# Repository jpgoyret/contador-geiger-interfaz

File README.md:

# Interfaz de manejo y visualización de los datos de un contador Geiger-Müller en microcontrolador de 8 bits

## Descripcion:
Dispositivo para controlar y recibir información de un detector de partículas radioactivas. Este informa la cantidad de partículas que han sido recibidas en un intervalo de tiempo deseado y, en particular, comunica cuando se ha superado un umbral de radiación establecido por el usuario.

El primer prototipo funcional de este proyecto fue realizado en el marco de la materia "6609/8607 Laboratorio de Microcontroladores" en la Facultad de Ingeniería de la Universidad de Buenos Aires (FIUBA).

La intrerfaz fue desarrollada sobre un microcontrolador de 8 bits Atmega328p (integrado en un Arduino) y programada en Assembly.

## Navegación del repositorio

En el archivo [Documentacion_Contador_Geiger](Documentacion_Contador_Geiger.pdf) se podrá encontrar la documentación propia de la interfaz incluyendo: breve descripción del desarrollo, diagramas de flujo y de bloques, componentes de la interfaz, conexiones, entre otros.

En [Mediciones_Contador_Geiger](Mediciones_Contador_Geiger.pdf) se incluyen las mediciones realizadas sobre el contador Geiger por medio de la interfaz de manejo y visualización de datos. Para dichas pruebas se empleó una fuente elevadora de tensión elaborada por Ing. Ricardo Arias.

#### Carpetas:

- Codigo: incluye el código fuente del programa que irá embebido en el microcontrolador Atmega328p. Dicho código puede ser copiado y pegado dentro de la carpeta de un proyecto de Atmel Studio para poder ser modificado.
- diseño_caja_contador_geiger: contiene los archivos 3D del diseño de una caja que contenga a la fuente elevadora de tensión armada en una placa de 10cmx10cm.
- esquematicos: contiene los esquemáticos del PCB del shield del Arduino y del teclado.

## Integrantes del equipo:
- Nuñez Frau, Federico
- Vidal, Gabriel
- Goyret, Juan Pablo

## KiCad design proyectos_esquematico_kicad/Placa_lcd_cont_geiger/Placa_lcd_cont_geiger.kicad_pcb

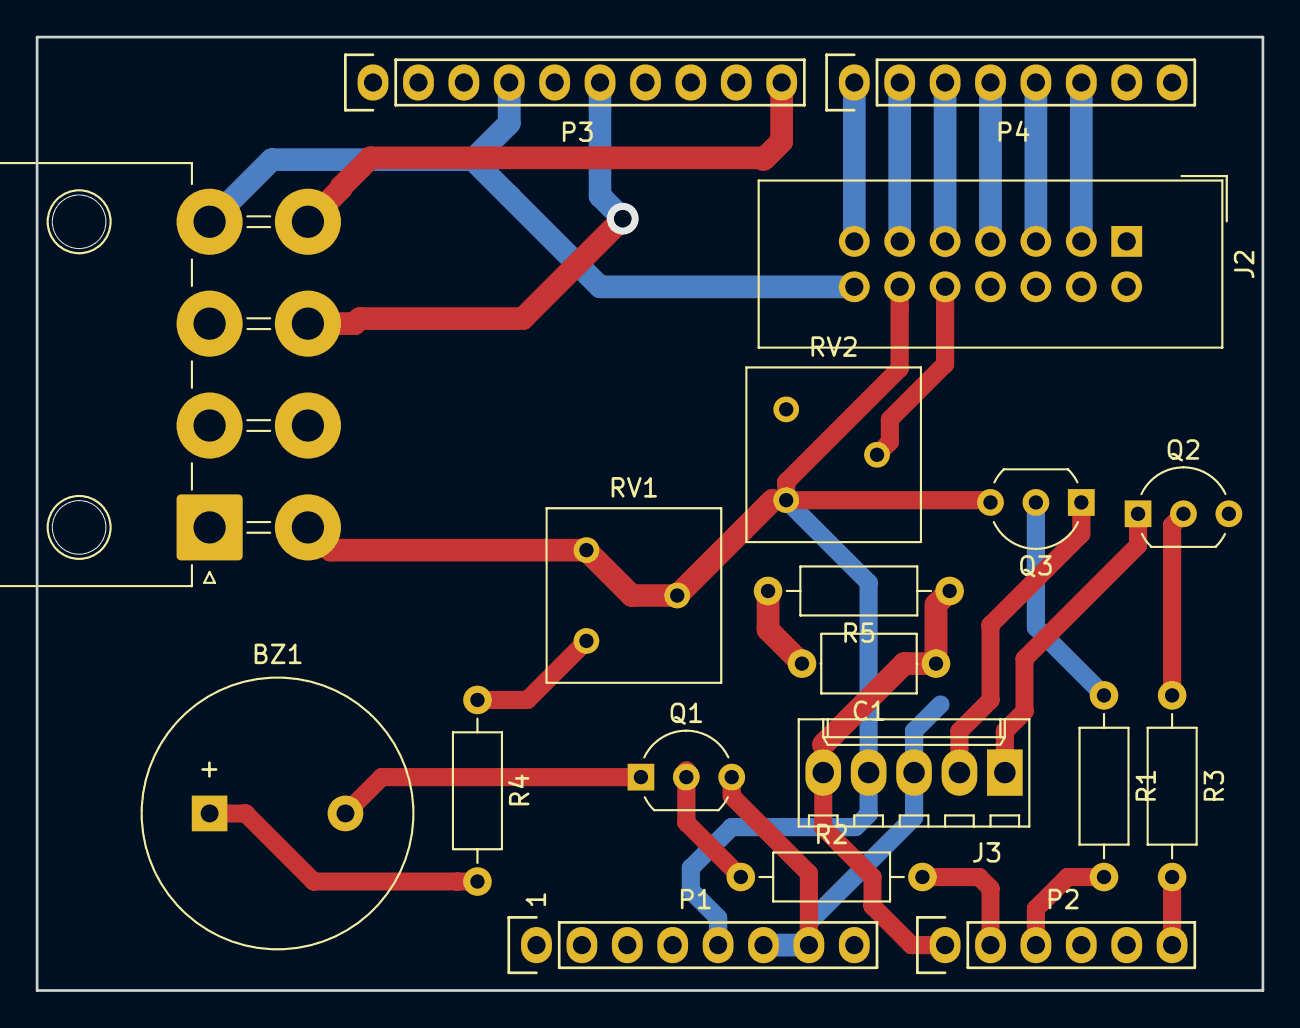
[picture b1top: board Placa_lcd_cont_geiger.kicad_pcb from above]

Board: 2 copper layers, 68.6 x 53.3 mm, 19 parts (0 on the bottom side), 23 nets.

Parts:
BZ1: Buzzer; Buzzer_15x7.5RM7.6
C1: 0.01u; C_Axial_L5.1mm_D3.1mm_P7.50mm_Horizontal
J1: Conn_02x04_Counter_Clockwise; Molex_Mega-Fit_76825-0008_2x04_P5.70mm_Horizontal
J2: Conn_01x14_Female; IDC-Header_2x07_P2.54mm_Vertical
J3: Conn_01x05_Female; Molex_KK-6410-05_05x2.54mm_Straight
P1: Power; Socket_Strip_Arduino_1x08
P2: Analog; Socket_Strip_Arduino_1x06
P3: Digital; Socket_Strip_Arduino_1x10
P4: Digital; Socket_Strip_Arduino_1x08
Q1, Q2: BC548; TO-92_Inline_Wide
Q3: BC558; TO-92_Inline_Wide
R1, R2, R3: 10k; R_Axial_DIN0207_L6.3mm_D2.5mm_P10.16mm_Horizontal
R4: 100; R_Axial_DIN0207_L6.3mm_D2.5mm_P10.16mm_Horizontal
R5: 100k; R_Axial_DIN0207_L6.3mm_D2.5mm_P10.16mm_Horizontal
RV1: 500; Potentiometer_Bourns_3386F_Vertical
RV2: 10k; Potentiometer_Bourns_3386F_Vertical

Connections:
/2: J2.3, P4.6
/3(**): J2.5, P4.5
/4: J2.7, P4.4
/5(**): J2.9, P4.3
/6(**): J2.11, P4.2
/7: J2.13, P4.1
/8: J1.8, P3.10
/12(MISO): J1.7, P3.6
/A0: C1.1, J3.5, P2.1, R5.1
/A1: P2.2, R2.2
/A2: P2.3, R1.2
/A5: P2.6, R3.2
GND: C1.2, J1.4, J2.14, J3.3, P1.6, P1.7, P3.4, Q1.3, Q2.3, R5.2, RV2.3
unnamed: BZ1.1, R4.2
unnamed: BZ1.2, Q1.1
unnamed: J2.10, RV2.2
unnamed: J3.1, Q2.1
unnamed: J3.2, Q3.1
unnamed: Q1.2, R2.1
unnamed: Q2.2, R3.1
unnamed: Q3.2, R1.1
unnamed: R4.1, RV1.1
VCC: J1.5, J2.12, J3.4, P1.5, Q3.3, RV1.2, RV1.3, RV2.1

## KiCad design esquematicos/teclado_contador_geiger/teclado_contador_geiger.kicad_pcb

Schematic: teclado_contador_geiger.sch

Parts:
D1: LED ROJO; LED_D5.0mm
D2: LED VERDE; LED_D5.0mm
J1: Conn_01x05_Female; Molex_KK-6410-05_05x2.54mm_Straight
R1: 82k; R_0805_2012Metric_Pad1.15x1.40mm_HandSolder
R2: 47k; R_0805_2012Metric_Pad1.15x1.40mm_HandSolder
R3: 33k; R_0805_2012Metric_Pad1.15x1.40mm_HandSolder
R4: 22k; R_0805_2012Metric_Pad1.15x1.40mm_HandSolder
R5: 15k; R_0805_2012Metric_Pad1.15x1.40mm_HandSolder
R6, R7: 220; R_0805_2012Metric_Pad1.15x1.40mm_HandSolder
SW1, SW2, SW3, SW4, SW5, SW6: SW_SPST; SW_PUSH_6mm

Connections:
+5V: J1.2, R6.1, SW1.2 (B), SW2.2 (B), SW3.2 (B), SW4.2 (B), SW5.2 (B), SW6.2 (B)
/teclado_out: J1.1, R5.2, SW6.1 (A)
GND: D2.1 (K), J1.3
unnamed: D1.1 (K), J1.5
unnamed: D1.2 (A), R6.2
unnamed: D2.2 (A), R7.2
unnamed: J1.4, R7.1
unnamed: R1.1, SW1.1 (A)
unnamed: R1.2, R2.1, SW2.1 (A)
unnamed: R2.2, R3.1, SW3.1 (A)
unnamed: R3.2, R4.1, SW4.1 (A)
unnamed: R4.2, R5.1, SW5.1 (A)

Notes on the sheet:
CANCELAR
FLECHA ABAJO
FLECHA DERECHA
FLECHA ARRIBA
FLECHA IZQUIERDA

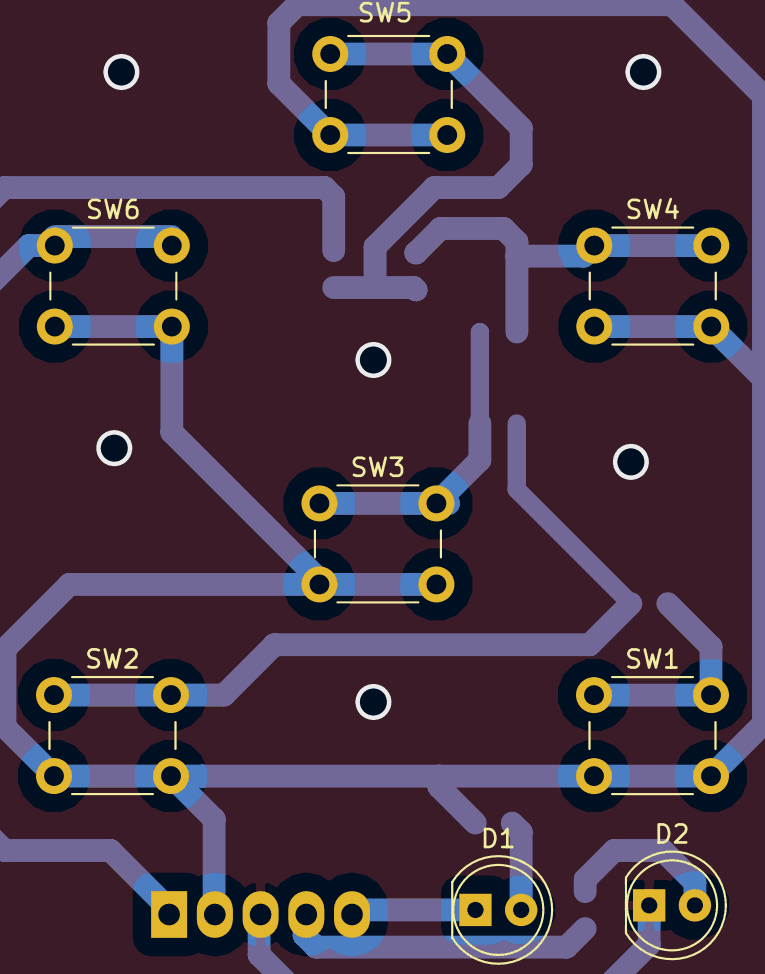
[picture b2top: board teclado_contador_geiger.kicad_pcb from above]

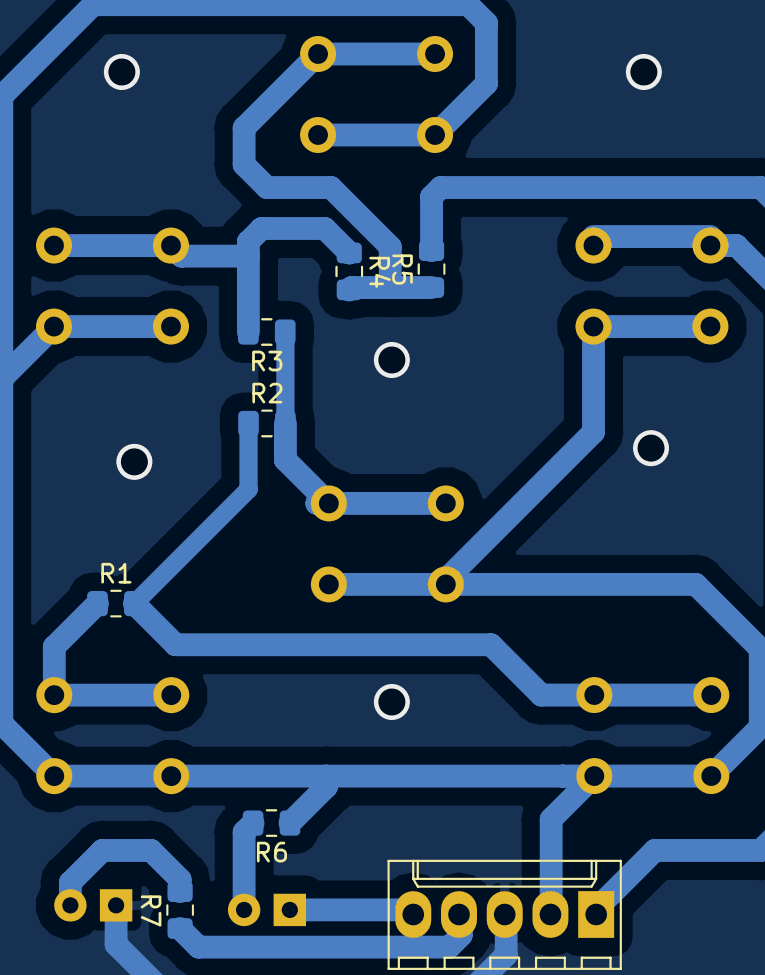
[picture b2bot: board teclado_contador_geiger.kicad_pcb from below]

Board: 2 copper layers, 16 parts (8 on the bottom side), 12 nets.

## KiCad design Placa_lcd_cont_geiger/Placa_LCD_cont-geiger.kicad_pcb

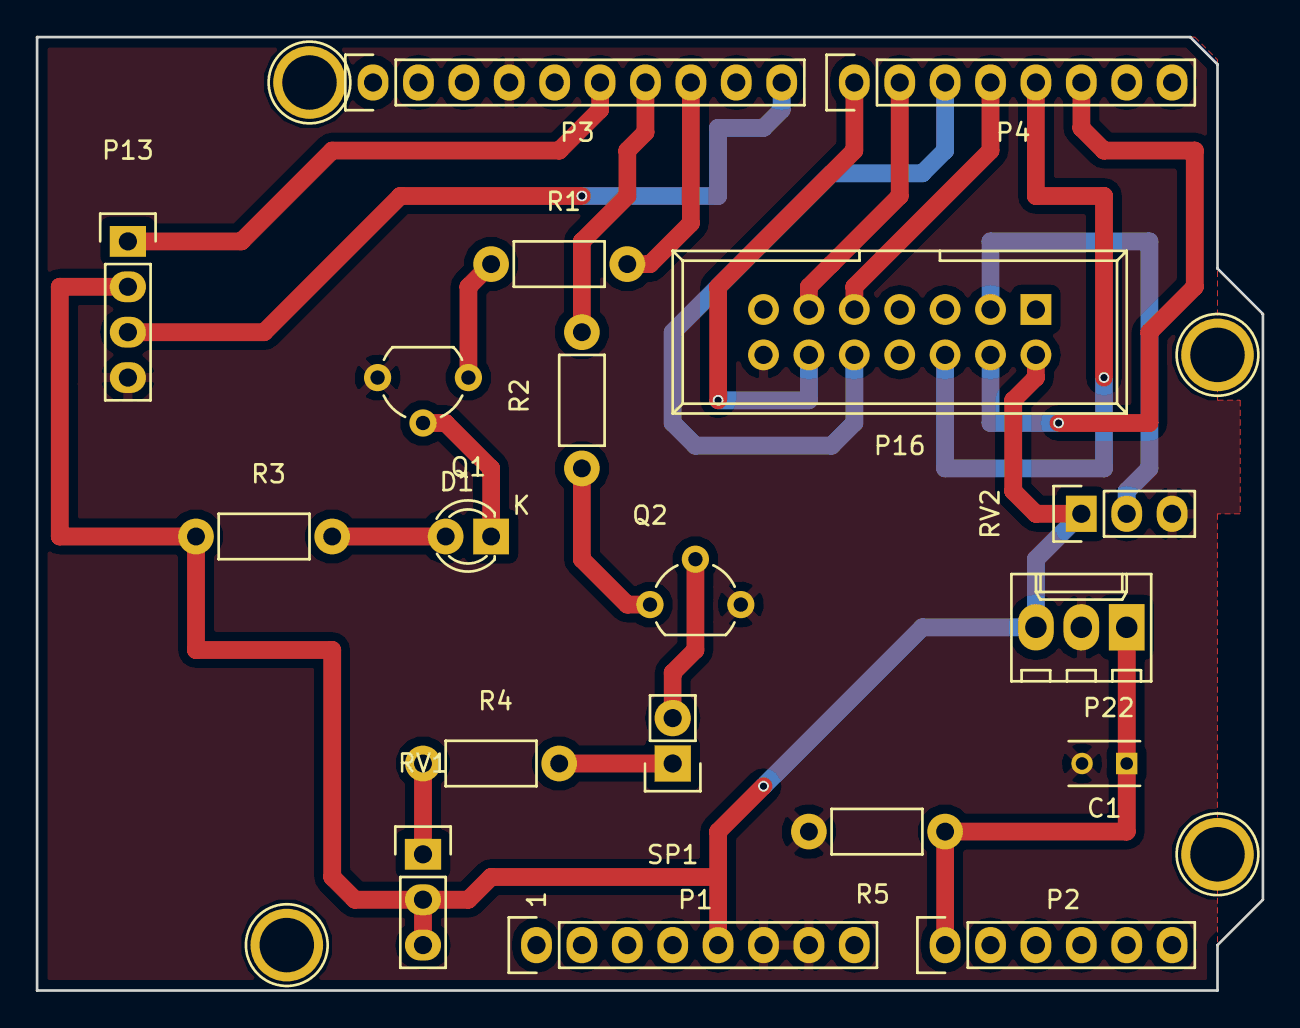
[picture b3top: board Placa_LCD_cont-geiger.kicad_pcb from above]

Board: 2 copper layers, 68.6 x 53.3 mm, 23 parts (0 on the bottom side), 23 nets.

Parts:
C1: 0.1u; C_Rect_L4_W2.5_P2.5
D1: LED; LED-3MM
P1: Power; Socket_Strip_Arduino_1x08
P2: Analog; Socket_Strip_Arduino_1x06
P3: Digital; Socket_Strip_Arduino_1x10
P4: Digital; Socket_Strip_Arduino_1x08
P5, P6, P7, P8: CONN_01X01; Arduino_1pin
P13: X2EHDV-4P; Pin_Header_Straight_1x04
P16: IDC_14; IDC_Header_Straight_14pins
P22: CONN_PLACA_TECLADO; Molex_KK-6410-03_03x2.54mm_Straight
Q1: BC548/BC547; TO-92_Molded_Wide
Q2: BC547/BC548; TO-92_Molded_Wide
R1, R2: 10k; Resistor_Horizontal_RM7mm
R3: 220; Resistor_Horizontal_RM7mm
R4: 100; Resistor_Horizontal_RM7mm
R5: 100k; Resistor_Horizontal_RM7mm
RV1, RV2: POT; Pin_Header_Straight_1x03
SP1: BUZZER; Pin_Header_Straight_1x02

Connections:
/2: P4.6, P16.4
/3(**): P4.5, P16.6
/4: P4.4, P16.9
/5(**): P4.3, P16.10
/6(**): P4.2, P16.11
/7: P4.1, P16.12
/8: P3.10, P13.3
/10(**/SS): P3.8, R1.2
/11(**/MOSI): P3.7, R2.2
/12(MISO): P3.6, P13.1
/A0: C1.1, P2.1, P22.1, R5.1
/A4(SDA): P2.5, P3.2
/A5(SCL): P2.6, P3.1
GND: C1.2, P1.6, P1.7, P3.4, P13.4, P16.14, P22.2, Q1.3, Q2.3, R5.2, RV2.3
unnamed: D1.1, Q1.2
unnamed: D1.2, R3.2
unnamed: P16.3, RV2.2
unnamed: Q1.1, R1.1
unnamed: Q2.1, R2.1
unnamed: Q2.2, SP1.2
unnamed: R4.1, RV1.1
unnamed: R4.2, SP1.1
VCC: P1.5, P13.2, P16.2, P22.3, R3.1, RV1.2, RV1.3, RV2.1

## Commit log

2019-02-22 Primer commit despues del clone del repo de labo de micro
2019-03-11 Mejora en la documentacion y cambios menores
2019-04-29 Agregado del CAD de la caja
2019-08-16 Subo los archivos del PCB del LCD y teclado
2019-08-16 Esquemático de la placa del LCD en KiCad v5
2019-08-17 Actualización del PCB del shield
2019-08-18 Agregado del PCB del teclado
2019-08-18 Agregado del PCB del teclado(2)
2019-08-21 Cambios varios en la documentación
2019-08-23 Agregado de LED verde a la placa del teclado e incremento de las dimensiones de esta última incluyendo una mayor separación entre los botones
2019-08-26 Agrega PCB del teclado
2019-08-29 Se modificó distancia entre dos resistencias de la placa teclado
2019-09-12 Modificaciones en el PCB para poder mardarlo a hacer al LCI. Agregado del esquematico del Arduino UNO R3 actualizado a la carpeta 'doc'
2019-09-12 Actualizacion de los gerbers y de los drills (cambios necesarios para poder mandar a hacer las placas al LCI)
2019-09-23 Se sube el archivo de la caja completo
2019-10-15 Empieza PCB del LCD
2019-10-24 Cambios en el código para integrar el encendido y apagado del led verde
2019-10-28 Agregado de la funcionalidad para medir infinitas ventanas y corrección de bugs
2019-12-23 Se agrega routeo LCD PCB
2020-01-10 Cambios menores al PCB del LCD
2020-01-13 Cambio del pin del buzzer
2020-01-15 Cambios menores en el shield para adaptarlo a los cambios hechos sobre el prototipo
2020-01-15 Cambios menores en el shield para adaptarlo a los cambios hechos sobre el prototipo(1)
